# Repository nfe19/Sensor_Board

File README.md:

# Sensor_Board
A PCB board with firmware to control sensors

This project looks at a PCB design and looks at an implementation of firmware to design somthing useful with the sensors

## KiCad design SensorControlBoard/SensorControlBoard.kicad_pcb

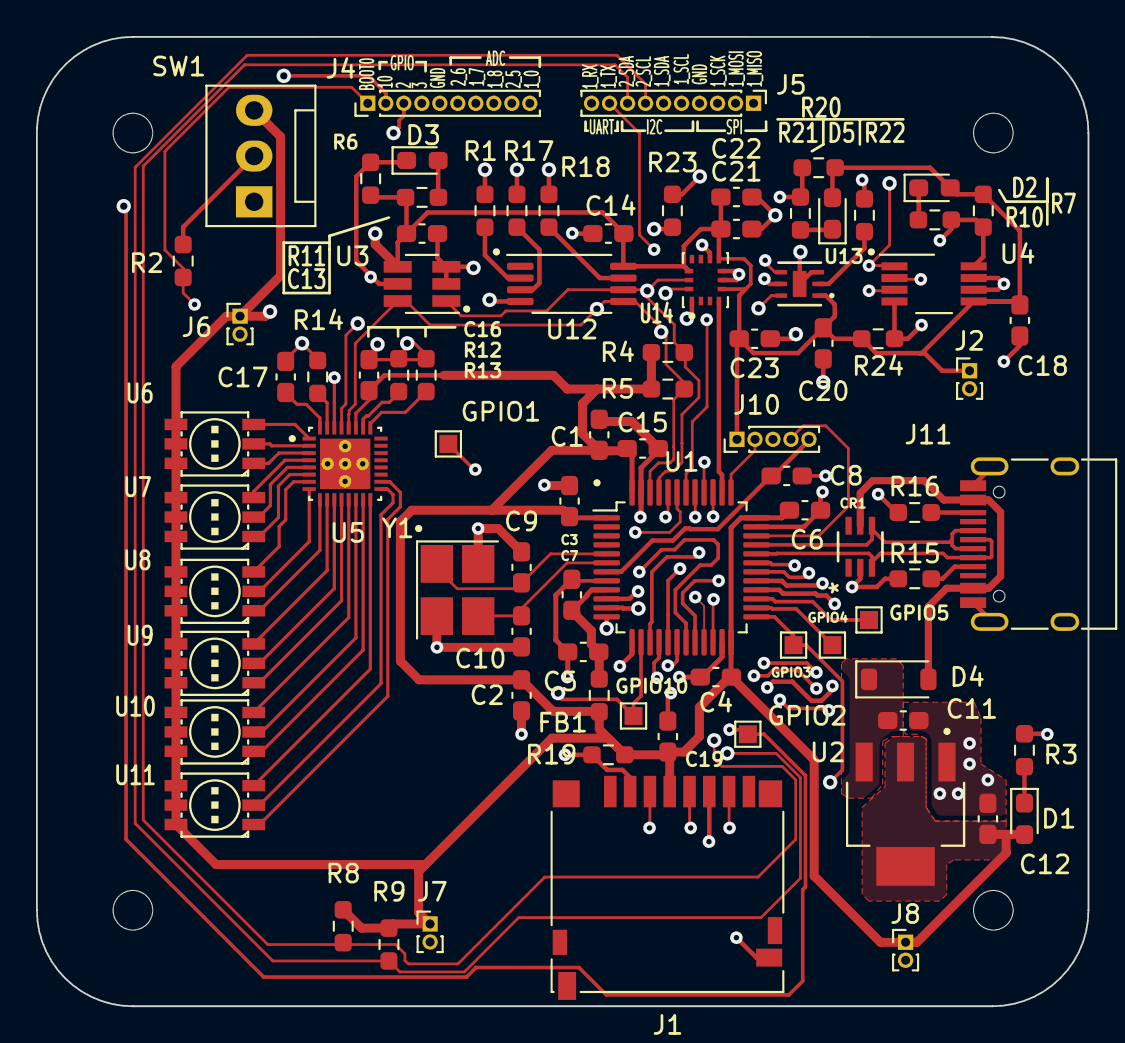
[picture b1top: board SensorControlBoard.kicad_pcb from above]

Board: 4 copper layers, 58.4 x 53.9 mm, 89 parts (0 on the bottom side), 75 nets.

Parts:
C1: 10u; C_0603_1608Metric_Pad1.08x0.95mm_HandSolder
C2, C5, C11, C12, C13, C14, C16, C17, C18, C19, C20, C22: 1u; C_0603_1608Metric_Pad1.08x0.95mm_HandSolder
C3, C4, C6, C8, C15, C21, C23: 100n; C_0603_1608Metric_Pad1.08x0.95mm_HandSolder
C7: 10n; C_0603_1608Metric_Pad1.08x0.95mm_HandSolder
C9, C10: 10p; C_0603_1608Metric_Pad1.08x0.95mm_HandSolder
CR1: NUP4114UCLW1T2G; SC-88&slash_SC70-6&slash_SOT-363_419B-02_ONS_OSI-M
D1: Red; LED_0603_1608Metric_Pad1.05x0.95mm_HandSolder
D2, D3, D5: Yellow; LED_0603_1608Metric_Pad1.05x0.95mm_HandSolder
D4: SM5817PL-TP; D_SOD-123
FB1: 120R; R_0603_1608Metric_Pad0.98x0.95mm_HandSolder
GPIO1, GPIO2, GPIO3, GPIO4, GPIO5, GPIO10: TestPoint; TestPoint_Pad_1.0x1.0mm
H1, H2, H3, H4: MountingHole; MountingHole_2.2mm_M2
J1: Micro_SD_Card; microSD_HC_Hirose_DM3D-SF
J2, J6, J7, J8: Conn_01x02_Pin; PinHeader_1x02_P1.00mm_Vertical
J4, J5: Conn_01x10_Pin; PinHeader_1x10_P1.00mm_Vertical
J10: Conn_01x05_Pin; PinHeader_1x05_P1.00mm_Vertical
J11: USB_C_Receptacle_USB2.0; USB_C_Receptacle_HRO_TYPE-C-31-M-12
R1, R2, R3, R4, R5, R6, R7, R8, R9, R10, R11, R12, R13, R17, R18, R19, R21, R22, R23, R24: 1K5; R_0603_1608Metric_Pad0.98x0.95mm_HandSolder
R14: 3K; R_0603_1608Metric_Pad0.98x0.95mm_HandSolder
R15, R16, R20: 5K1; R_0603_1608Metric_Pad0.98x0.95mm_HandSolder
SW1: SW_SPDT; FanPinHeader_1x03_P2.54mm_Vertical
U1: STM32F103C8T6TR; LQFP-48_7x7mm_P0.5mm
U2: TLV1117LV33DCYR; VREG_TLV1117LV33DCYR
U3: TMAG5273B1QDBVR; SOT-23-6_Handsoldering
U4: TMAG5170-Q1; VSSOP-8_3.0x3.0mm_P0.65mm
U5: LP5018RSMR; QFN40P400X400X100-33N
U6, U7, U8, U9, U10, U11: ASMB-TTF0-0A20B; PLCC-6
U12: AT24CS04-XHM; TSSOP-8_4.4x3mm_P0.65mm
U13: OPT3002DNPR; DNP6_TEX
U14: ICM-42670-P; XDCR_ICM-42670-P
Y1: 16MHz OSC; Crystal_SMD_3225-4Pin_3.2x2.5mm_HandSoldering

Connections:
+3.3V: C1.1, C2.1, C3.1, C4.1, C6.1, C12.1, C13.1, C14.1, C15.1, C16.1, C18.1, C19.1, C20.1, C21.1, C22.1, C23.1, D1.2 (A), D2.2 (A), D5.2 (A), FB1.1, J1.4 (VDD), J2.1, J6.1, J7.1, J8.1, J10.1, R4.2, R5.2, R6.1, R7.1, R8.1, R9.1, R11.2, R19.1, R20.2, R24.1, SW1.3 (C), U1.1 (VBAT), U1.24 (VDD), U1.36 (VDD), U1.48 (VDD), U2.2 (OUT_2), U2.4 (OUT_4), U3.4 (VCC), U4.5 (VCC), U5.27 (VCC), U6.1, U6.3, U6.5, U7.1, U7.3, U7.5, U8.1, U8.3, U8.5, U9.1, U9.3, U9.5, U10.1, U10.3, U10.5, U11.1, U11.3, U11.5, U12.8 (VCC), U13.1 (VDD), U14.5 (VDDIO), U14.8 (VDD), U14.12 (AP_CS)
+3.3VA: C5.1, C7.1, FB1.2, U1.9 (VDDA)
/Peripherals/5273_INT_IND_A: D3.2 (A), R11.1
/Peripherals/AT24CS04-XHM_A1: R1.2, U12.2 (A1)
/Peripherals/AT24CS04-XHM_A2: R17.2, U12.3 (A2)
/Peripherals/AT24CS04-XHM_WP: R18.2, U12.7 (WP)
/Peripherals/LED0_B: U5.3 (OUT2), U6.6
/Peripherals/LED0_G: U5.2 (OUT1), U6.4
/Peripherals/LED0_R: U5.1 (OUT0), U6.2
/Peripherals/LED1_B: U5.6 (OUT5), U7.6
/Peripherals/LED1_G: U5.5 (OUT4), U7.4
/Peripherals/LED1_R: U5.4 (OUT3), U7.2
/Peripherals/LED2_B: U5.9 (OUT8), U8.6
/Peripherals/LED2_G: U5.8 (OUT7), U8.4
/Peripherals/LED2_R: U5.7 (OUT6), U8.2
/Peripherals/LED3_B: U5.12 (OUT11), U9.6
/Peripherals/LED3_G: U5.11 (OUT10), U9.4
/Peripherals/LED3_R: U5.10 (OUT9), U9.2
/Peripherals/LED4_B: U5.15 (OUT14), U10.6
/Peripherals/LED4_G: U5.14 (OUT13), U10.4
/Peripherals/LED4_R: U5.13 (OUT12), U10.2
/Peripherals/LED5_B: U5.18 (OUT17), U11.6
/Peripherals/LED5_G: U5.17 (OUT16), U11.4
/Peripherals/LED5_R: U5.16 (OUT15), U11.2
/uController/ADC1_0: J4.10, U1.10 (PA0)
/uController/ADC1_7: J4.7, U1.17 (PA7)
/uController/ADC1_8: J4.8, U1.18 (PB0)
/uController/ADC2_5: J4.9, U1.15 (PA5)
/uController/ADC2_6: J4.6, U1.16 (PA6)
/uController/BOOT0: J4.1, R2.1, U1.44 (BOOT0)
/uController/BOOT0_PP: R2.2, SW1.2 (B)
/uController/I2C2_SCL: J5.7, R9.2, U1.21 (PB10)
/uController/I2C2_SDA: J5.8, R8.2, U1.22 (PB11)
/uController/NRST: C8.1, J10.5, U1.7 (NRST)
/uController/OSC_IN: C9.1, U1.5 (PD0), Y1.1
/uController/OSC_OUT: C10.1, U1.6 (PD1), Y1.3
/uController/PWR_LED_K: D1.1 (K), R3.2
/uController/SWCLK: J10.2, U1.37 (PA14)
/uController/SWDIO: J10.4, U1.34 (PA13)
/uController/UART1_RX: J5.10, U1.43 (PB7)
/uController/UART1_TX: J5.9, U1.42 (PB6)
/uController/USB+: CR1.4, J11.A6 (D+), J11.B6 (D+), U1.33 (PA12)
/uController/USB-: CR1.3, J11.A7 (D-), J11.B7 (D-), U1.32 (PA11)
/uController/VBUS_USB: CR1.5, D4.2 (A), J11.A4 (VBUS), J11.A9 (VBUS), J11.B4 (VBUS), J11.B9 (VBUS)
GND: C1.2, C2.2, C3.2, C4.2, C5.2, C6.2, C7.2, C8.2, C9.2, C10.2, C11.2, C12.2, C13.2, C14.2, C15.2, C16.2, C17.2, C18.2, C19.2, C20.2, C21.2, C22.2, C23.2, CR1.2, J1.6 (VSS), J1.9 (SHIELD), J2.2, J4.5, J5.4, J6.2, J7.2, J8.2, J10.3, J11.A1 (GND), J11.A12 (GND), J11.B1 (GND), J11.B12 (GND), J11.S1 (SHIELD), R1.1, R3.1, R12.1, R13.1, R14.1, R15.1, R16.1, R17.1, R18.1, R22.1, R23.1, SW1.1 (A), U1.8 (VSSA), U1.23 (VSS), U1.35 (VSS), U1.47 (VSS), U2.1 (GND), U3.2 (GND), U3.3 (TEST), U4.6 (GND), U4.7 (TEST), U5.33 (GND), U5.34 (GND), U5.35 (GND), U5.36 (GND), U5.37 (GND), U5.38 (GND), U12.4 (GND), U13.3 (GND), U13.7 (EPAD), U14.6 (GND), U14.7 (FSYNC), Y1.2, Y1.4
GPIO_1: GPIO1.1, U1.19 (PB1)
GPIO_2: GPIO2.1, J4.3, U1.20 (PB2)
GPIO_3: GPIO3.1, J4.4, U1.25 (PB12)
GPIO_4: GPIO4.1, U1.26 (PB13)
GPIO_5: GPIO5.1, U1.27 (PB14)
GPIO_6: R7.2, R10.2, U1.28 (PB15), U4.8 (~ALERT)
GPIO_7: D3.1 (K), R6.2, U1.11 (PA1), U3.5 (~INT)
GPIO_8: U1.12 (PA2), U5.30 (EN)
GPIO_9: J1.2 (DAT3/CD), R19.2, U1.13 (PA3)
GPIO_10: GPIO10.1, J4.2, U1.14 (PA4)
GPIO_11: R24.2, U1.29 (PA8), U4.4 (~CS)
GPIO_12: R20.1, R21.2, U1.30 (PA9), U13.5 (INT)
GPIO_13: U1.31 (PA10), U14.9 (INT2)
GPIO_14: U1.38 (PA15), U14.4 (INT1/INT)
I2C1_SCL: J5.5, R4.1, U1.45 (PB8), U3.1 (CLK), U5.29 (SCL), U12.6 (SCL), U13.4 (SCL), U14.13 (AP_SCL/AP_SCLK)
I2C1_SDA: J5.6, R5.1, U1.46 (PB9), U3.6 (SDA), U5.28 (SDA), U12.5 (SDA), U13.6 (SDA), U14.14 (AP_SDA/AP_SDIO/AP_SDI)
unnamed: D2.1 (K), R10.1
unnamed: D5.1 (K), R21.1
unnamed: J11.A5 (CC1), R15.2
unnamed: J11.B5 (CC2), R16.2
unnamed: R13.2, U5.25 (ADDR0)
unnamed: R12.2, U5.26 (ADDR1)
unnamed: R14.2, U5.31 (IRF)
unnamed: C17.1, U5.32 (VCAP)
unnamed: R22.2, U13.2 (ADDR)
unnamed: R23.2, U14.1 (AP_SDO/AP_AD0)
SPI1_MISO: J1.7 (DAT0), J5.1, U1.40 (PB4), U4.3 (MISO)
SPI1_MOSI: J1.3 (CMD), J5.2, U1.41 (PB5), U4.2 (MOSI)
SPI1_SCK: J1.5 (CLK), J5.3, U1.39 (PB3), U4.1 (SCLK)
VBUS: C11.1, D4.1 (K), U2.3 (IN)

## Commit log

2024-06-29 Update to README
2024-07-06 implementation of the OPT3002 light sensor
2024-07-07 Implemented ICM-42670-P 6 axis gyroscope/accelerometer
2024-07-11 Added more schematic documentation to prepare for hardware layout
2024-08-17 Initial placement done
2024-09-29 Initial Routing finished
2024-10-04 added TVS protection diodes
2025-01-30 A0 PCB Commit
2025-01-30 git cleanup
2025-03-21 updated documentation
2025-03-29 pdf upload of schematic
